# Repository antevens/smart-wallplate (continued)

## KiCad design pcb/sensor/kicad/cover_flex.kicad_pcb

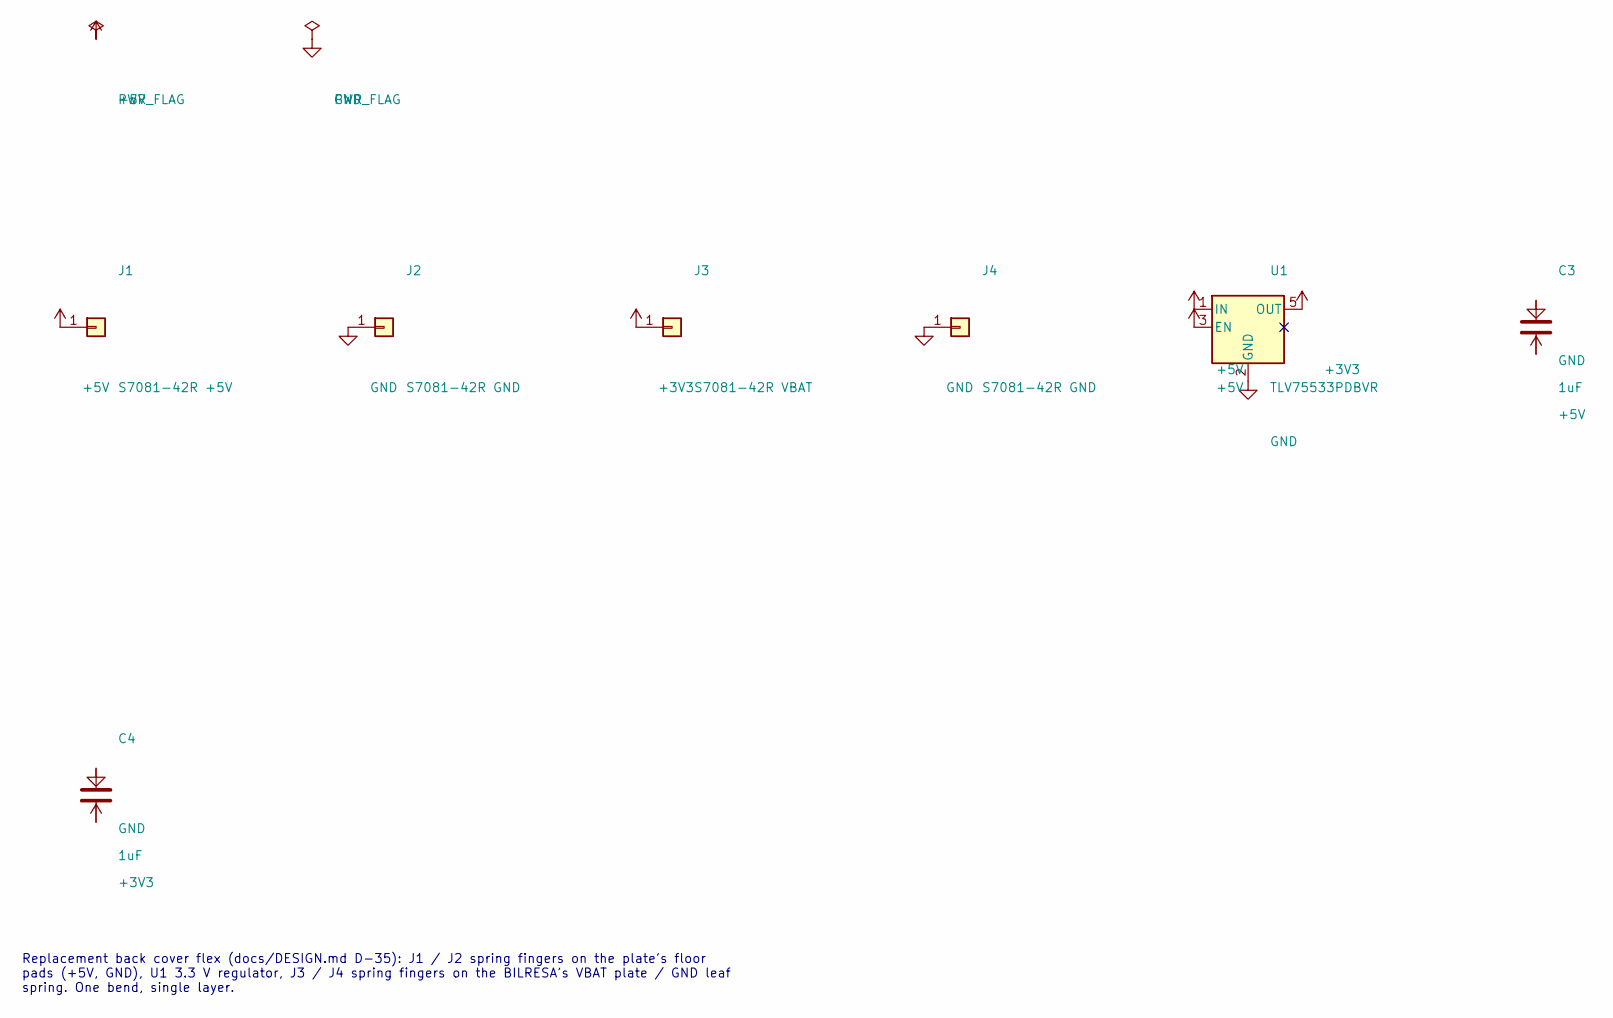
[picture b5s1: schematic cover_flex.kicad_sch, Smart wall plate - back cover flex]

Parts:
C3, C4: 1uF; C_0402_1005Metric; MPN GRM155R61A105KE15D
J1: S7081-42R +5V; Harwin_S7081-42R; MPN S7081-42R
J2, J4: S7081-42R GND; Harwin_S7081-42R; MPN S7081-42R
J3: S7081-42R VBAT; Harwin_S7081-42R; MPN S7081-42R
U1: TLV75533PDBVR; SOT-23-5; MPN TLV75533PDBVR

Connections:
+3V3: C4.2, J3.1, U1.5 (OUT)
+5V: C3.2, J1.1, U1.1 (IN), U1.3 (EN)
GND: C3.1, C4.1, J2.1, J4.1, U1.2 (GND)

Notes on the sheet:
Replacement back cover flex (docs/DESIGN.md D-35): J1 / J2 spring fingers on the plate's floor pads (+5V, GND), U1 3.3 V regulator, J3 / J4 spring fingers on the BILRESA's VBAT plate / GND leaf spring. One bend, single layer.

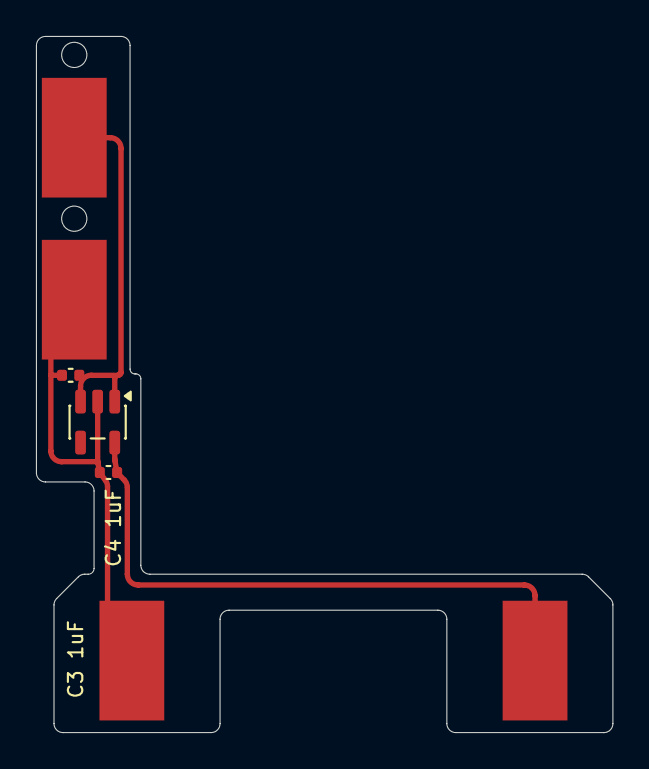
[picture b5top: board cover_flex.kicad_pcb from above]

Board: 2 copper layers, 32.0 x 38.7 mm, 7 parts (0 on the bottom side), 3 nets.

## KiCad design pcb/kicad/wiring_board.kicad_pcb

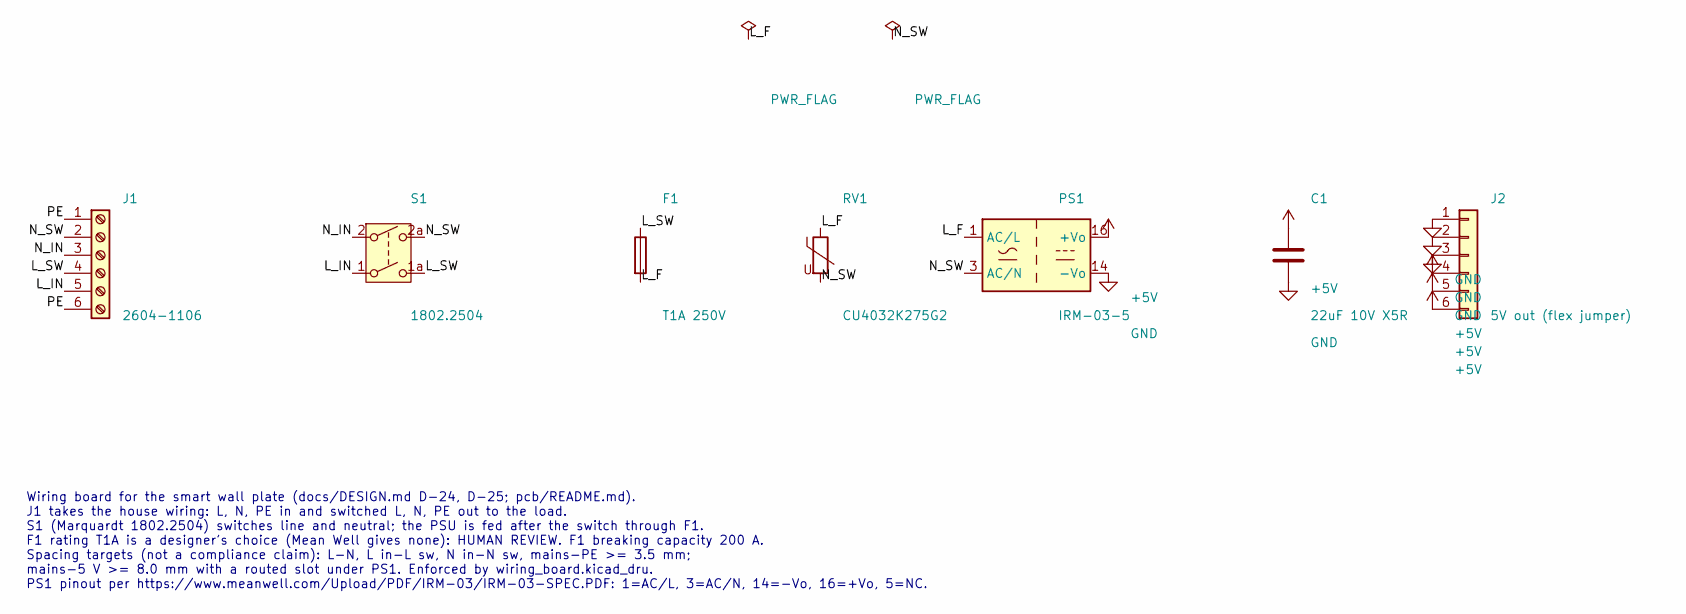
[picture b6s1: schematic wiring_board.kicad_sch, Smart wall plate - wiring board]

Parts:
C1: 22uF 10V X5R; C_1206_3216Metric; MPN GRM31CR61A226KE19L
F1: T1A 250V; Fuse_Schurter_UMT250; MPN 3404.2416.22
J1: 2604-1106; WAGO_2604-1106_1x06_P5.00mm_Horizontal; MPN 2604-1106
J2: 5V out (flex jumper); Hirose_FH12-6S-0.5SH_1x06-1MP_P0.50mm_Horizontal; MPN FH12-6S-0.5SH(55)
PS1: IRM-03-5; Converter_ACDC_MeanWell_IRM-03-xx_THT; MPN IRM-03-5
RV1: CU4032K275G2; Varistor_TDK_CU4032; MPN B72660M0271K093
S1: 1802.2504; Marquardt_1802.2504_DPST_PCB; MPN 1802.2504

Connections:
+5V: C1.1, J2.4, J2.5, J2.6, PS1.16 (+Vo)
/L_F: F1.2, PS1.1 (AC/L), RV1.1
/L_IN: J1.5, S1.1
/L_SW: F1.1, J1.4, S1.1a (2)
/N_IN: J1.3, S1.2 (3)
/N_SW: J1.2, PS1.3 (AC/N), RV1.2, S1.2a (4)
/PE: J1.1, J1.6
GND: C1.2, J2.1, J2.2, J2.3, PS1.14 (-Vo)

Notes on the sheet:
Wiring board for the smart wall plate (docs/DESIGN.md D-24, D-25; pcb/README.md). J1 takes the house wiring: L, N, PE in and switched L, N, PE out to the load. S1 (Marquardt 1802.2504) switches line and neutral; the PSU is fed after the switch through F1. F1 rating T1A is a designer's choice (Mean 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

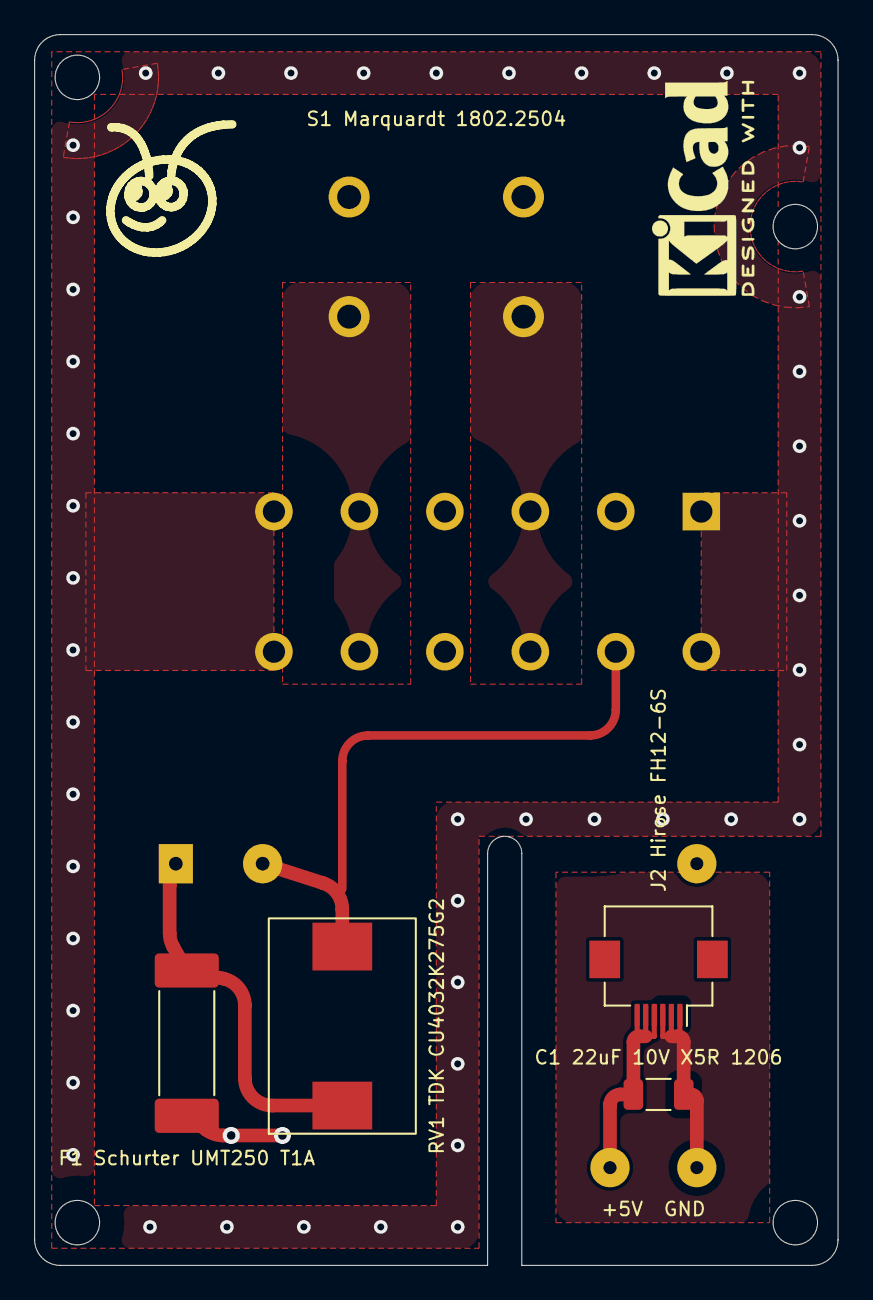
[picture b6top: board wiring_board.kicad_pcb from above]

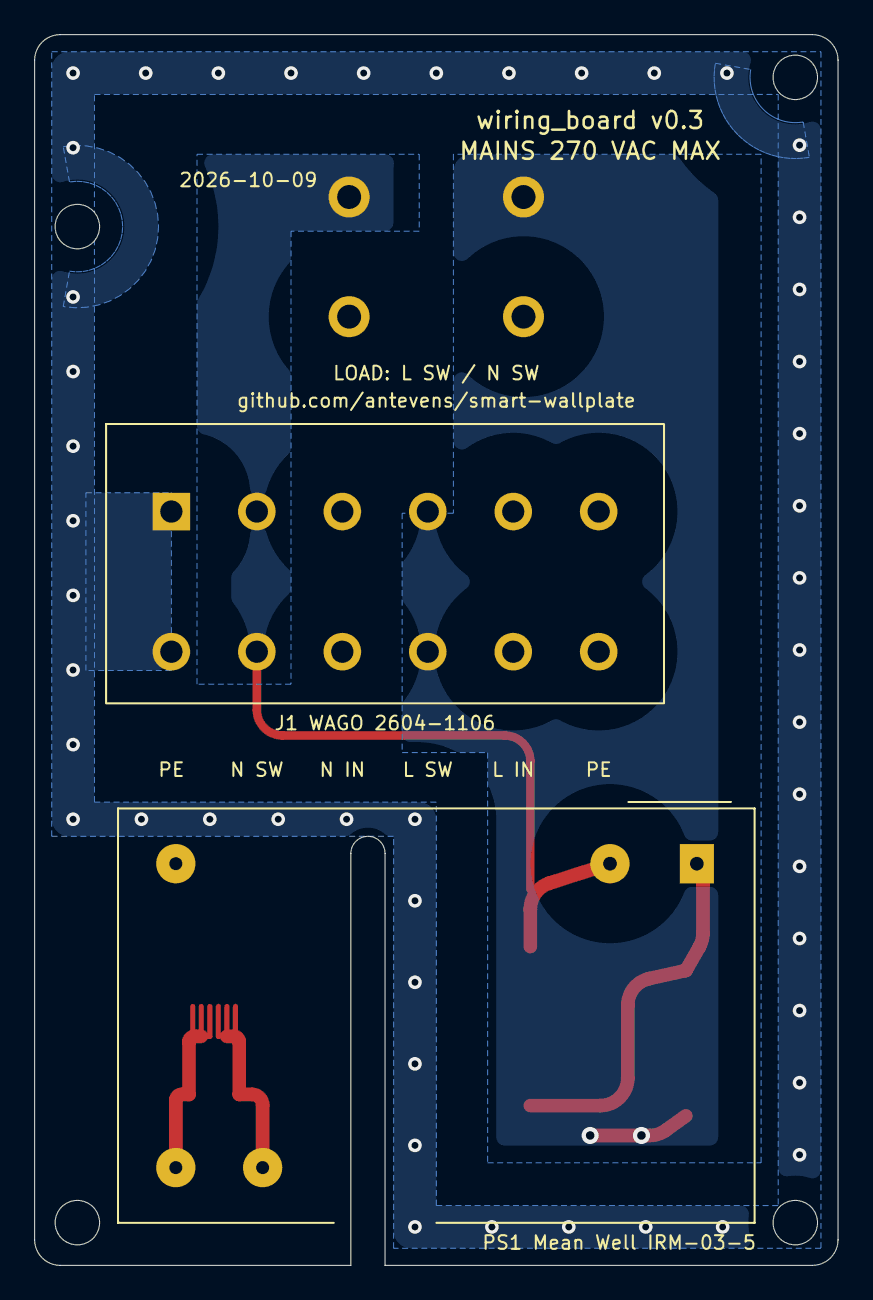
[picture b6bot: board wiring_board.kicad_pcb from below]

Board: 2 copper layers, 47.0 x 72.0 mm, 13 parts (2 on the bottom side), 8 nets.

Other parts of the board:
LOGO1: Ant_Logo_8mm_SilkScreen
LOGO2: KiCad-Logo2_5mm_SilkScreen
MH1, MH2, MH3, MH4: MountingHole_2.6mm_NPTH

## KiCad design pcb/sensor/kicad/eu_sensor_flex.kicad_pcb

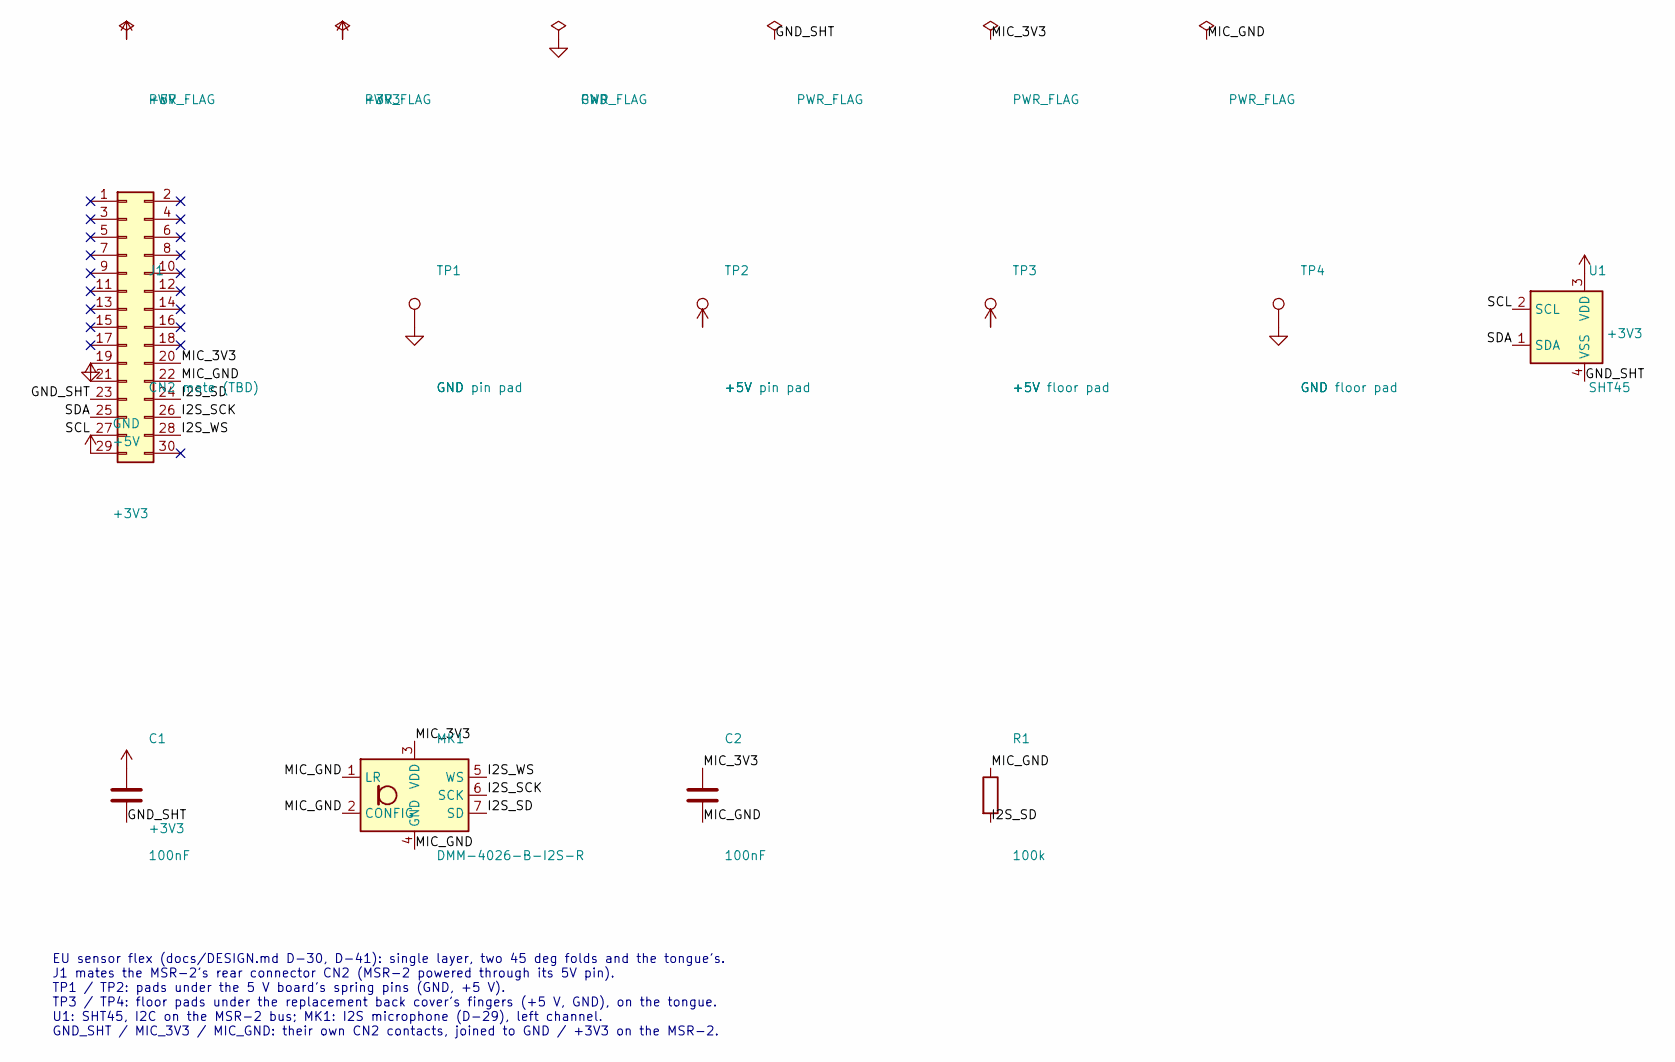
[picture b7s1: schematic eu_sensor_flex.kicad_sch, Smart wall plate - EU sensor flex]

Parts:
C1, C2: 100nF; C_0402_1005Metric; MPN 0402 X7R 100 nF 16 V
J1: CN2 mate (TBD); B2B_0.4mm_2x15_PLACEHOLDER; MPN TBD
MK1: DMM-4026-B-I2S-R; PUI_DMM-4026-B-I2S_4x3mm; MPN DMM-4026-B-I2S-R
R1: 100k; R_0402_1005Metric; MPN 0402 1% 100 kOhm
TP1: GND pin pad; Contact_Pad_D2.4mm
TP2: +5V pin pad; Contact_Pad_D2.4mm
TP3: +5V floor pad; Contact_Pad_2.9x7mm
TP4: GND floor pad; Contact_Pad_2.9x7mm
U1: SHT45; Sensirion_DFN-4_1.5x1.5mm_P0.8mm_SHT4x_NoCentralPad; MPN SHT45-AD1B-R2

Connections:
+3V3: C1.1, J1.29, U1.3 (VDD)
+5V: J1.21, TP2.1, TP3.1
/GND_SHT: C1.2, J1.23, U1.4 (VSS)
/I2S_SCK: J1.26, MK1.6 (SCK)
/I2S_SD: J1.24, MK1.7 (SD), R1.2
/I2S_WS: J1.28, MK1.5 (WS)
/MIC_3V3: C2.1, J1.20, MK1.3 (VDD)
/MIC_GND: C2.2, J1.22, MK1.1 (LR), MK1.2 (CONFIG), MK1.4 (GND), R1.1
/SCL: J1.27, U1.2 (SCL)
/SDA: J1.25, U1.1 (SDA)
GND: J1.19, TP1.1, TP4.1

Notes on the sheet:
EU sensor flex (docs/DESIGN.md D-30, D-41): single layer, two 45 deg folds and the tongue's. J1 mates the MSR-2's rear connector CN2 (MSR-2 powered through its 5V pin). TP1 / TP2: pads under the 5 V board's spring pins (GND, +5 V). TP3 / TP4: floor pads under the replacement back cover's fingers (+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

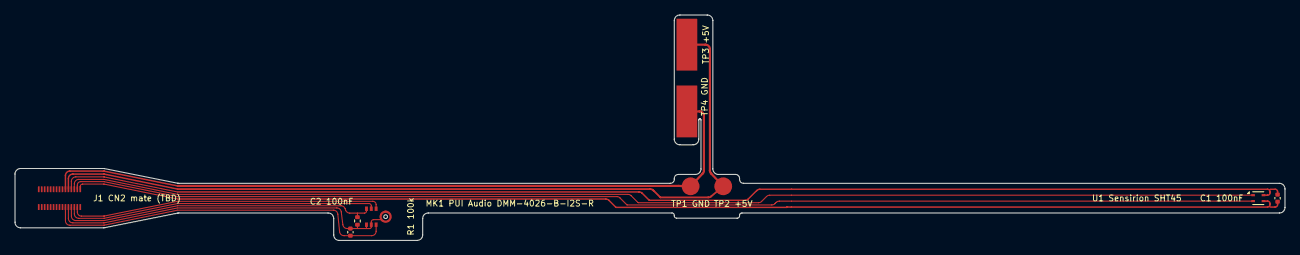
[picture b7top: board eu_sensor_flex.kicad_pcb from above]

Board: 2 copper layers, 171.3 x 30.4 mm, 10 parts (0 on the bottom side), 11 nets.

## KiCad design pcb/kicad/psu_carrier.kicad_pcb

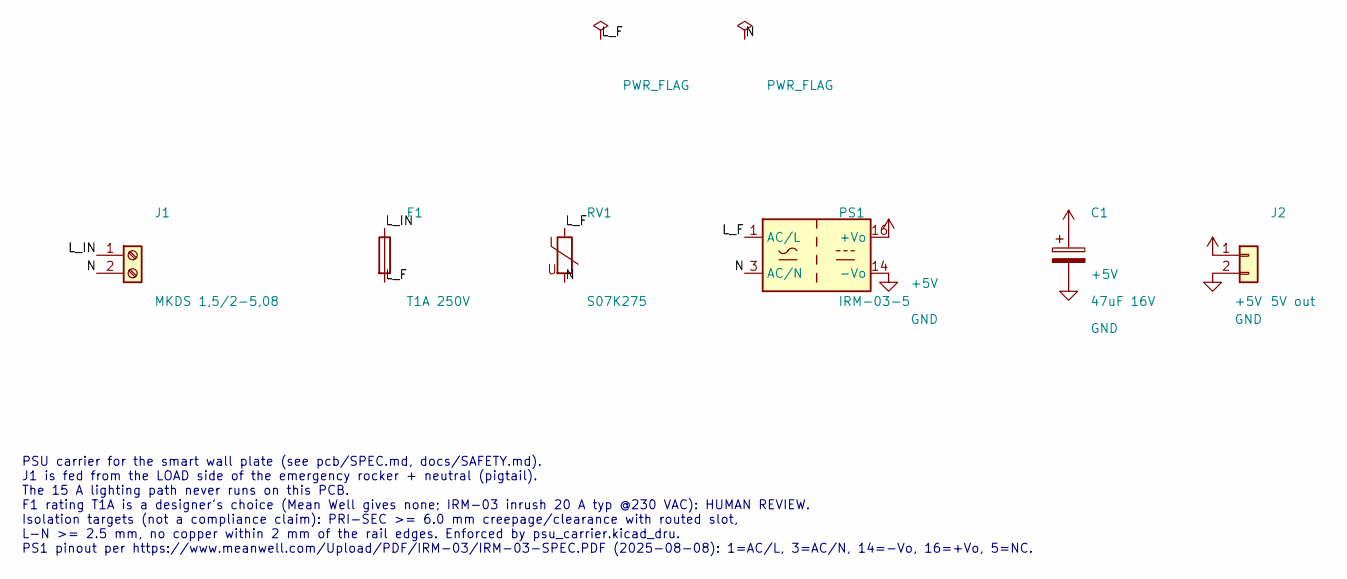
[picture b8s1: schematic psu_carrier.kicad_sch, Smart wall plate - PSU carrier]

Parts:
C1: 47uF 16V; CP_Radial_D5.0mm_P2.00mm; MPN EEU-FC1C470
F1: T1A 250V; Fuse_Littelfuse_372_D8.50mm; MPN 39211000000
J1: MKDS 1,5/2-5,08; TerminalBlock_Phoenix_MKDS-1,5-2-5.08_1x02_P5.08mm_Horizont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; MPN 1715721
J2: 5V out; JST_XH_B2B-XH-A_1x02_P2.50mm_Vertical; MPN B2B-XH-A(LF)(SN)
PS1: IRM-03-5; Converter_ACDC_MeanWell_IRM-03-xx_THT; MPN IRM-03-5
RV1: S07K275; RV_Disc_D7mm_W4.5mm_P5mm; MPN B72207S0271K101

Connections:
+5V: C1.1, J2.1, PS1.16 (+Vo)
/L_F: F1.2, PS1.1 (AC/L), RV1.1
/L_IN: F1.1, J1.1
/N: J1.2, PS1.3 (AC/N), RV1.2
GND: C1.2, J2.2, PS1.14 (-Vo)

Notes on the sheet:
PSU carrier for the smart wall plate (see pcb/SPEC.md, docs/SAFETY.md). J1 is fed from the LOAD side of the emergency rocker + neutral (pigtail). The 15 A lighting path never runs on this PCB. F1 rating T1A is a designer's choice (Mean Well gives none; IRM-03 inrush 20 A typ @230 VAC): HUMAN REVIEW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

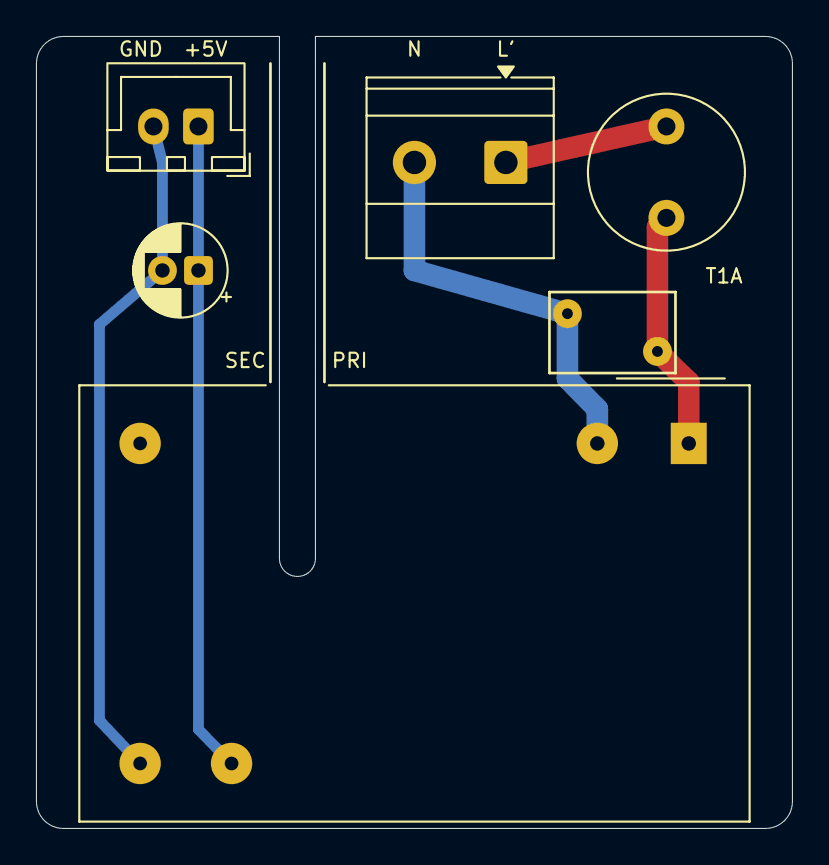
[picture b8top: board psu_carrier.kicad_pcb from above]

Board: 2 copper layers, 42.0 x 44.0 mm, 6 parts (0 on the bottom side), 5 nets.

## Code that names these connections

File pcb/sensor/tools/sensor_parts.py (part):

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# need not cross the others on the single copper layer.
CN2_MAP = {"I2S_WS": "19", "I2S_SCK": "21", "I2S_SD": "23", "MIC_GND": "25", "MIC_3V3": "27", "+5V": "29",
           "+3V3": "24", "SCL": "26", "SDA": "28", "GND": "30"}
I2S_GPIO = {"I2S_SCK": "IO4", "I2S_WS": "IO6", "I2S_SD": "IO7"}   # MSR-2 GPIOs (D-29), free on CN2


FP_B2B = "B2B_0.4mm_2x15_PLACEHOLDER"
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                      "7": "I2S_SD"},
                pos=(MIC_XC, MIC_FLEX_Y, 90), mfr="PUI Audio", mpn="DMM-4026-B-I2S-R",
                desc="I2S MEMS microphone, bottom port, 1.62-3.63 V; LR low = left channel", ds=MIC_DS),
    "C2": dict(label="100nF", sym="C", fp=FP_C, value="100nF", nets={"1": "MIC_3V3", "2": "MIC_GND"},
               pos=(MIC_XC + 2.8, 1.0, 90), mfr="any", mpn="0402 X7R 100 nF 16 V",
               desc="Microphone decoupling", ds=""),
    "R1": dict(label="100k", sym="R", fp=FP_R, value="100k", nets={"1": "I2S_SD", "2": "MIC_GND"},
               pos=(MIC_XC - 2.9, 2.0, 270), mfr="any", mpn="0402 1% 100 kOhm",
               desc="I2S SD pull-down (microphone datasheet)", ds=""),
}
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
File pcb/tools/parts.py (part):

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                nets={"1": "L_F", "3": "N_SW", "16": "+5V", "14": "GND", "5": "NC5"},
                pcb=None, mfr="Mean Well", mpn="IRM-03-5",
                desc="AC-DC module 85-305 VAC in, 5 V 600 mA, 37x24x15 mm", ds=IRM_DS),
    "F1": dict(label="Schurter UMT250 T1A", sym="Fuse", fp=FP_FUSE, value="T1A 250V", nets={"1": "L_SW", "2": "L_F"},
               pcb=(-14.6, -23.0, 90, "F"), mfr="Schurter", mpn="3404.2416.22",
               desc="SMD fuse UMT 250, time-lag 1 A 250 VAC. Rating is a designer's choice: human review",
               ds=UMT_DS),
    "RV1": dict(label="TDK CU4032K275G2", sym="Varistor", fp=FP_MOV, value="CU4032K275G2", nets={"1": "L_F", "2": "N_SW"},
                pcb=(-5.5, -22.0, 90, "F"), mfr="TDK", mpn="B72660M0271K093",
                desc="SMD varistor SIOV-CU4032K275G2K1, 275 VAC", ds=CU_DS),
    "C1": dict(label="22uF 10V X5R 1206", sym="C", fp=FP_C1, value="22uF 10V X5R", nets={"1": "+5V", "2": "GND"},
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    # in-pins (both J1 rows) straight up on the front
    ("L_IN", "F.Cu", [(-9.0, -2.0), (-1.5, -2.0), (-1.5, 21.5), (-9.0, 21.5)]),
    ("N_IN", "F.Cu", [(2.0, -2.0), (8.5, -2.0), (8.5, 21.5), (2.0, 21.5)]),
    # switched neutral: right of the N_IN pin, over the top to S1.2a (back)
    ("N_SW", "B.Cu", [(8.5, -2.0), (14.0, -2.0), (14.0, 29.0), (1.0, 29.0), (1.0, 24.5), (8.5, 24.5)]),
    # switched line (back): down from J1.4, under J1, up the left edge to S1.1a; also feeds F1
    ("L_SW", "B.Cu", [(2.0, 8.0), (2.0, -6.0), (-3.0, -6.0), (-3.0, -30.0), (-19.0, -30.0),
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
